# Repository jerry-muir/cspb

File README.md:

# Cluster System Power Board

## About

The Cluster System Power Board (CSPB) is a power distribution and control platform to simplify the construction of Single Board Computer Clusters. The power board is designed to allow for simple single cluster systems or complex multi board systems to be powered through one power supply and controlled from a single control module. Control of the power board is achieved via an i2c serial bus interface which can be chained across multiple power boards.
<br />

## The project
The project has three main components. The hardware design which can be found in the [Hardware](/Hardware) directory, the firmware code which can be found in the [Firmware](/Firmware) directory and some user interface software which can be found in the [Software](/Software) directory.

A detailed users manual can be found in the [Documents](\Documents)
 directory.
## Python package links:

[PIP cspb Package](https://pypi.org/project/cspb/)
<br />
[PIP cspb-tools Package](https://pypi.org/project/cspb-tools/)

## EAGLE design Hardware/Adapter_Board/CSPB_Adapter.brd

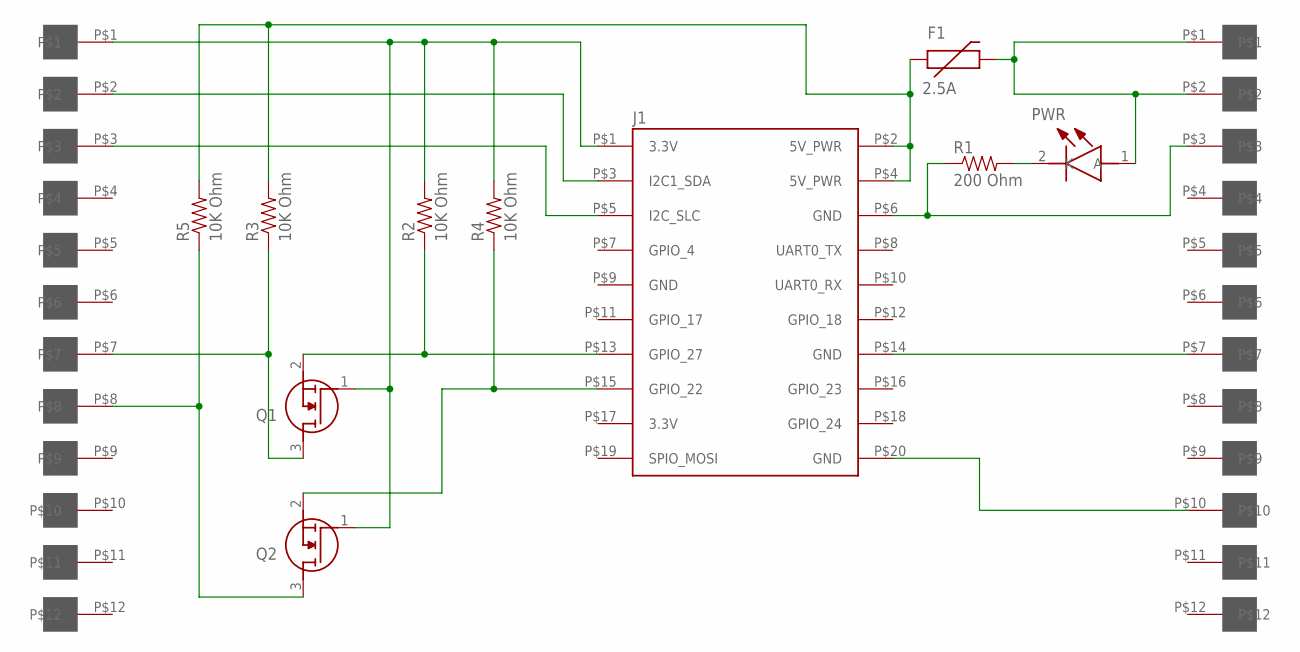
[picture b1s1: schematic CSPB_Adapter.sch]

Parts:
F1: 2.5A; F1812
J1: PPTC052LFBN-RC; 2X10_TH_HEADER_BOTTOM
J2, J3: 12_POS_BOARD_EDGE_PADS; CARD_EDGE_12_POS_0.1_IN
PWR: LTST-S220KGKT; LTSTS220KGKT
Q1, Q2: BSS138; SOT95P240X120-3N
R1: 200 Ohm; 0402-RES
R2, R3, R4, R5: 10K Ohm; 0402-RES

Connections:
3.3V: J1.P$1 (3.3V), J2.P$1, Q1.1 (G), Q2.1 (G), R2.2, R4.2
5V: F1.2, J3.P$1, J3.P$2, PWR.1 (A)
GND: J1.P$6 (GND), J1.P$9 (GND), J1.P$14 (GND), J1.P$20 (GND), J3.P$3, J3.P$7, J3.P$10, R1.1
MONITOR: J2.P$8, Q2.3 (D), R5.1
MONITOR_PI: J1.P$15 (GPIO_22), Q2.2 (S), R4.1
unnamed: F1.1, J1.P$2 (5V_PWR), J1.P$4 (5V_PWR), R3.2, R5.2
unnamed: PWR.2 (K), R1.2
SDA: J1.P$3 (I2C1_SDA), J2.P$2
SHUTDOWN: J2.P$7, Q1.3 (D), R3.1
SHUTDOWN_PI: J1.P$13 (GPIO_27), Q1.2 (S), R2.1
SLC: J1.P$5 (I2C_SLC), J2.P$3

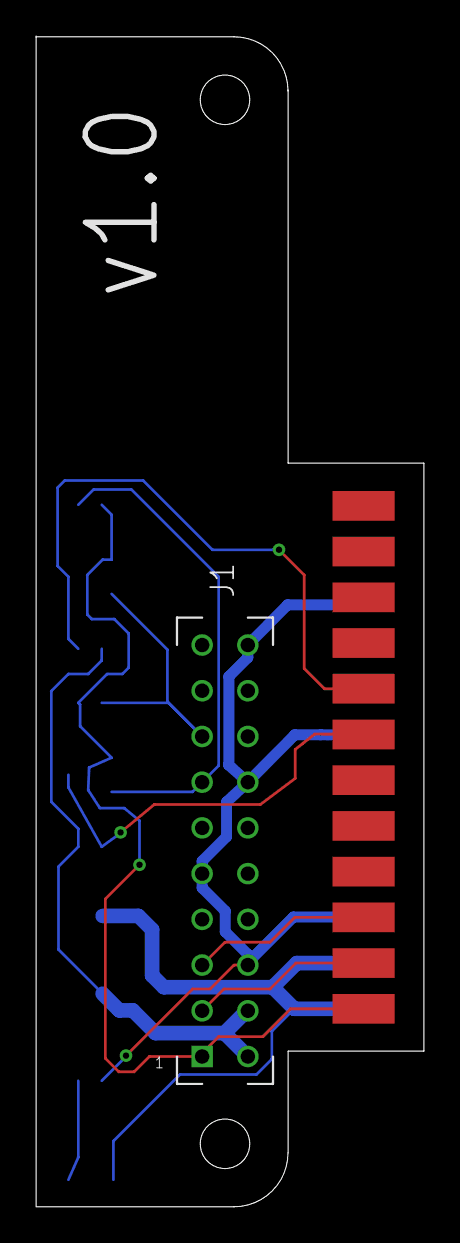
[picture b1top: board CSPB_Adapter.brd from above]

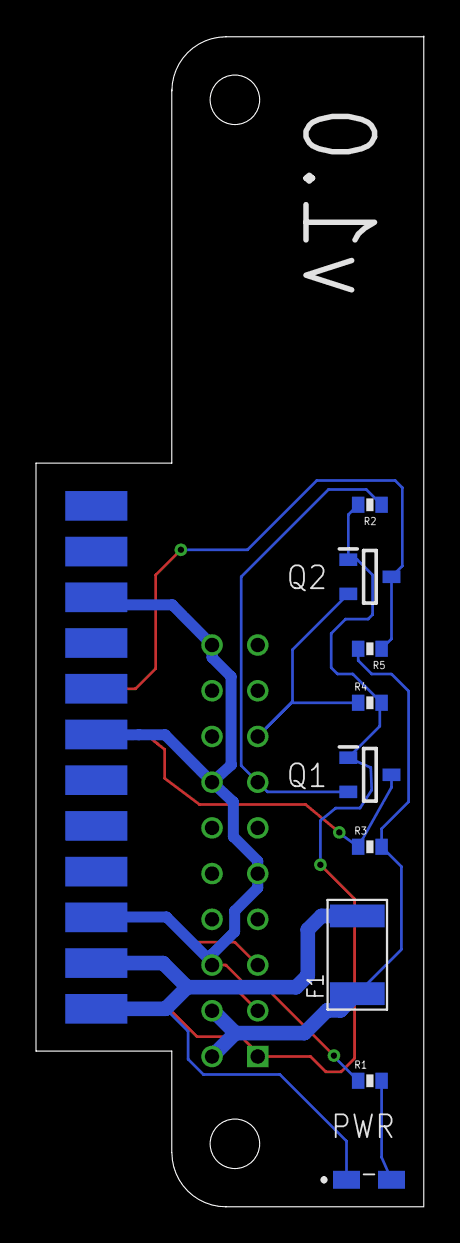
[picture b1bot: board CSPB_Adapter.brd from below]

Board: 2 copper layers, 21.6 x 65.0 mm, 12 parts (10 on the bottom side), 11 nets.

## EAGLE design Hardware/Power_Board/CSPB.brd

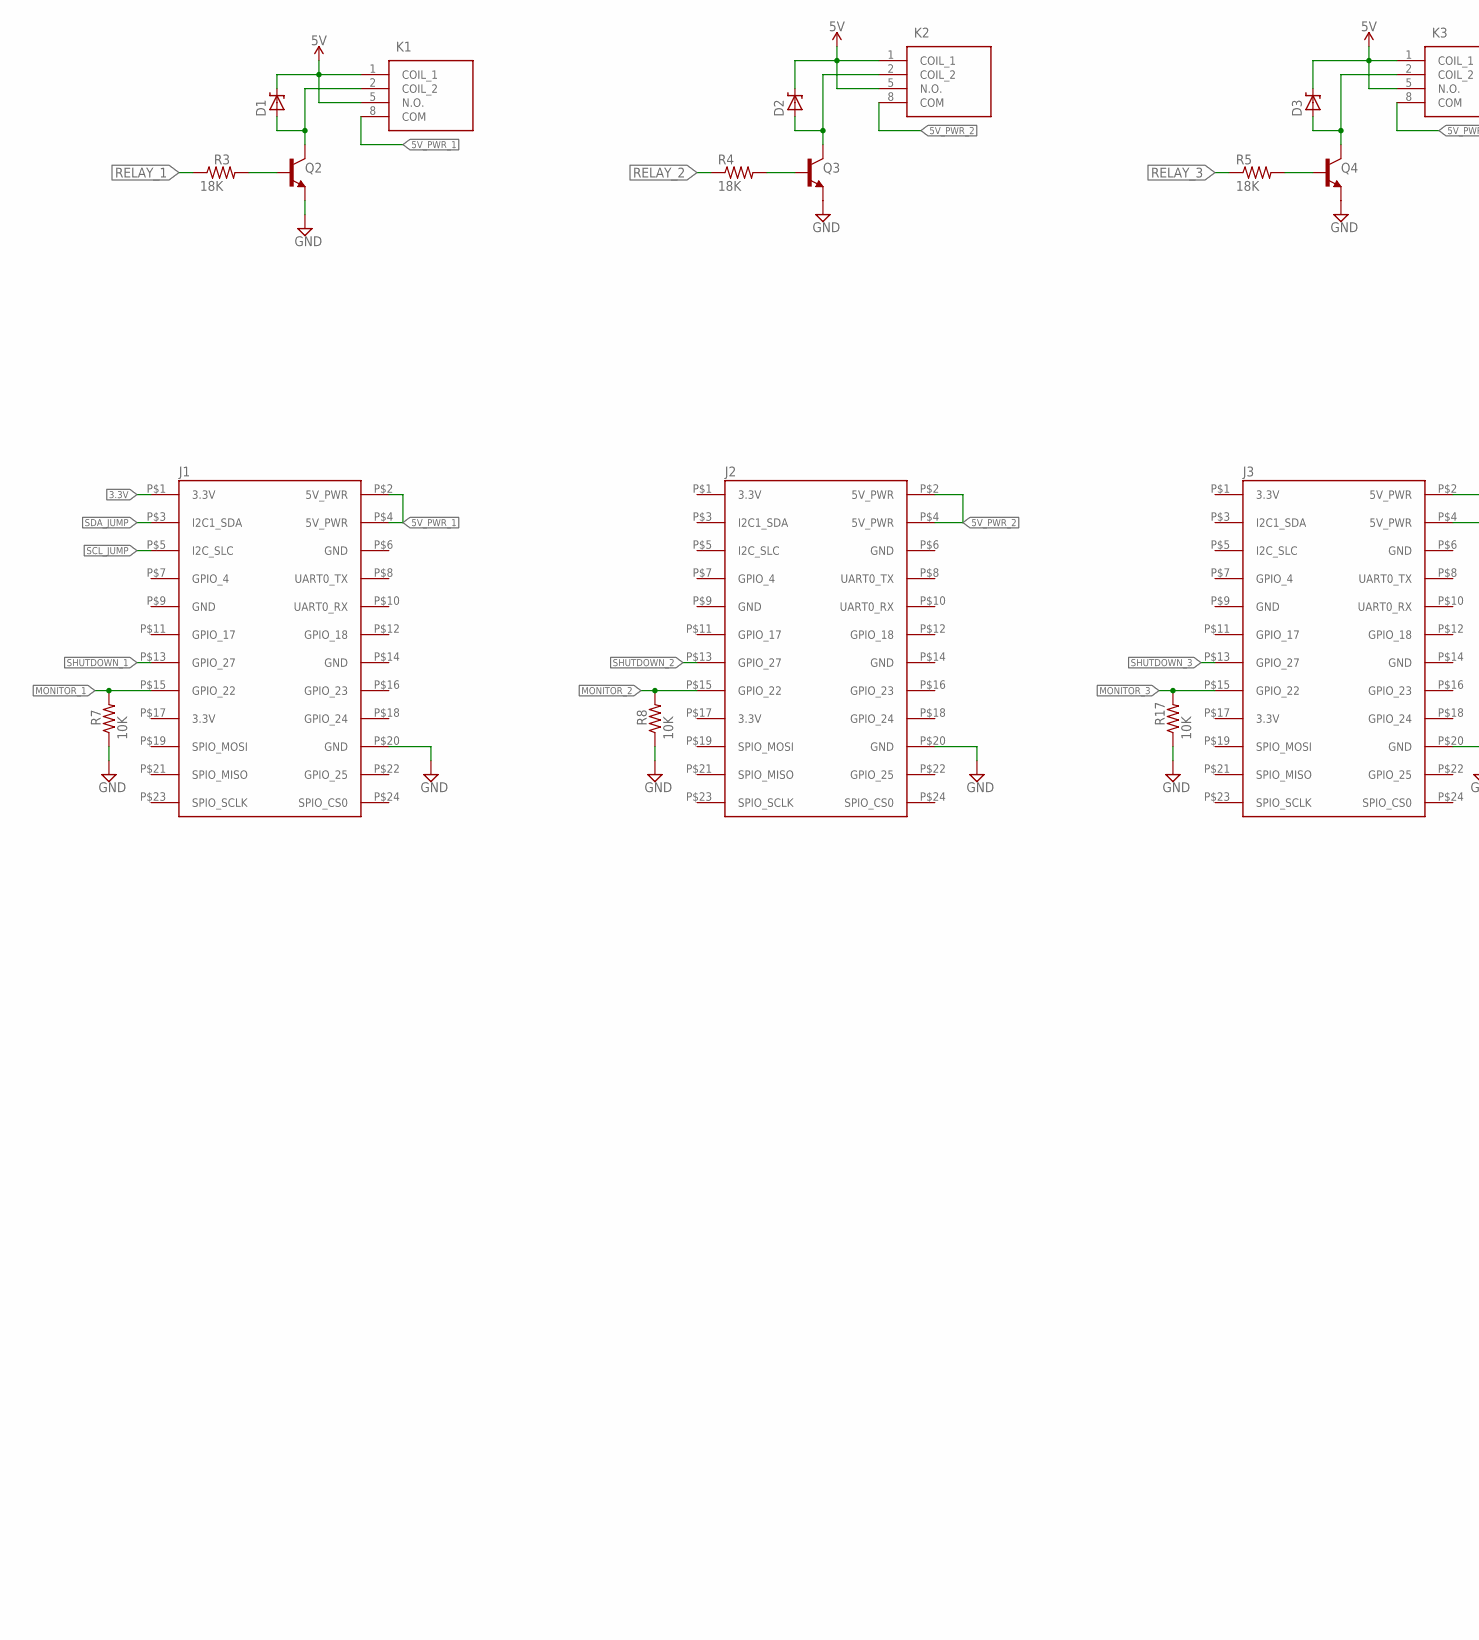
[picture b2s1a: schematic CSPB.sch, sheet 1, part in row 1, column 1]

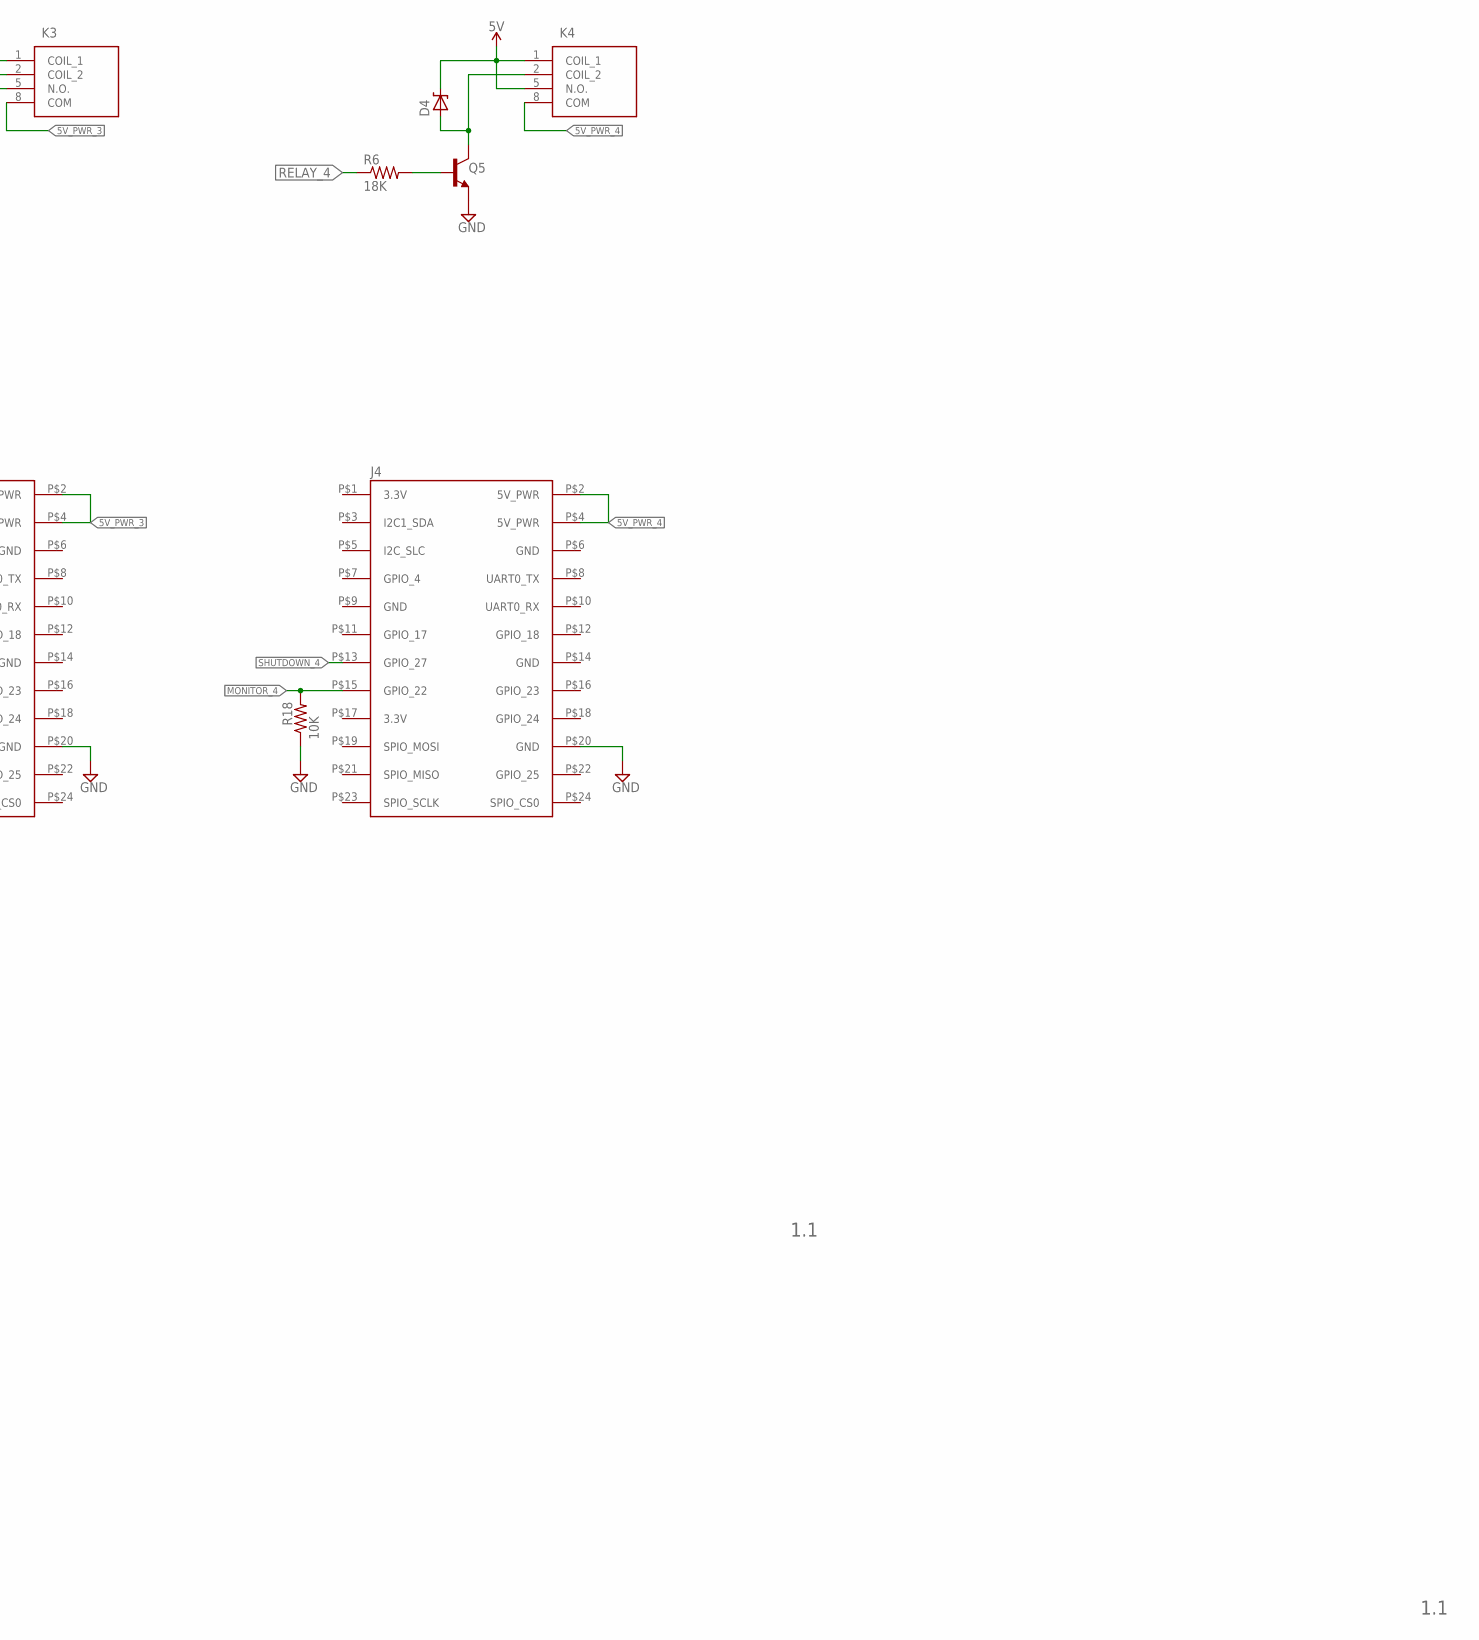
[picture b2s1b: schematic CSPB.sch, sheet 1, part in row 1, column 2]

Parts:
D1, D2, D3, D4: 1A/23V/620mV; SMADIODE
J1, J2, J3, J4: 5530843-1; 2X12_TH_EDGE_CONN
K1, K2, K3, K4: G6DN-1A_DC5; G6DN-1A-L
Q2, Q3, Q4, Q5: 600mA/40V; SOT23-3
R3, R4, R5, R6: 18K; 0603-RES
R7, R8, R17, R18: 10K; 0603-RES

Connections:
3.3V: J1.P$1 (3.3V); also elsewhere on the board
5V: D1.C, D2.C, D3.C, D4.C, K1.1 (COIL_1), K1.5 (N.O.), K2.1 (COIL_1), K2.5 (N.O.), K3.1 (COIL_1), K3.5 (N.O.), K4.1 (COIL_1), K4.5 (N.O.); also elsewhere on the board
5V_PWR_1: J1.P$2 (5V_PWR), J1.P$4 (5V_PWR), K1.8 (COM)
5V_PWR_2: J2.P$2 (5V_PWR), J2.P$4 (5V_PWR), K2.8 (COM)
5V_PWR_3: J3.P$2 (5V_PWR), J3.P$4 (5V_PWR), K3.8 (COM)
5V_PWR_4: J4.P$2 (5V_PWR), J4.P$4 (5V_PWR), K4.8 (COM)
GND: J1.P$6 (GND), J1.P$9 (GND), J1.P$14 (GND), J1.P$20 (GND), J2.P$6 (GND), J2.P$9 (GND), J2.P$14 (GND), J2.P$20 (GND), J3.P$6 (GND), J3.P$9 (GND), J3.P$14 (GND), J3.P$20 (GND), J4.P$6 (GND), J4.P$9 (GND), J4.P$14 (GND), J4.P$20 (GND), Q2.2 (E), Q3.2 (E), Q4.2 (E), Q5.2 (E), R7.1, R8.1, R17.1, R18.1; also elsewhere on the board
MONITOR_1: J1.P$15 (GPIO_22), R7.2; also elsewhere on the board
MONITOR_2: J2.P$15 (GPIO_22), R8.2; also elsewhere on the board
MONITOR_3: J3.P$15 (GPIO_22), R17.2; also elsewhere on the board
MONITOR_4: J4.P$15 (GPIO_22), R18.2; also elsewhere on the board
unnamed: Q2.1 (B), R3.2
unnamed: D1.A, K1.2 (COIL_2), Q2.3 (C)
unnamed: Q4.1 (B), R5.2
unnamed: Q5.1 (B), R6.2
unnamed: D2.A, K2.2 (COIL_2), Q3.3 (C)
unnamed: D3.A, K3.2 (COIL_2), Q4.3 (C)
unnamed: D4.A, K4.2 (COIL_2), Q5.3 (C)
unnamed: Q3.1 (B), R4.2
RELAY_1: R3.1; also elsewhere on the board
RELAY_2: R4.1; also elsewhere on the board
RELAY_3: R5.1; also elsewhere on the board
RELAY_4: R6.1; also elsewhere on the board
SCL_JUMP: J1.P$5 (I2C_SLC); also elsewhere on the board
SDA_JUMP: J1.P$3 (I2C1_SDA); also elsewhere on the board
SHUTDOWN_1: J1.P$13 (GPIO_27); also elsewhere on the board
SHUTDOWN_2: J2.P$13 (GPIO_27); also elsewhere on the board
SHUTDOWN_3: J3.P$13 (GPIO_27); also elsewhere on the board
SHUTDOWN_4: J4.P$13 (GPIO_27); also elsewhere on the board

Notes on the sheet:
1.1

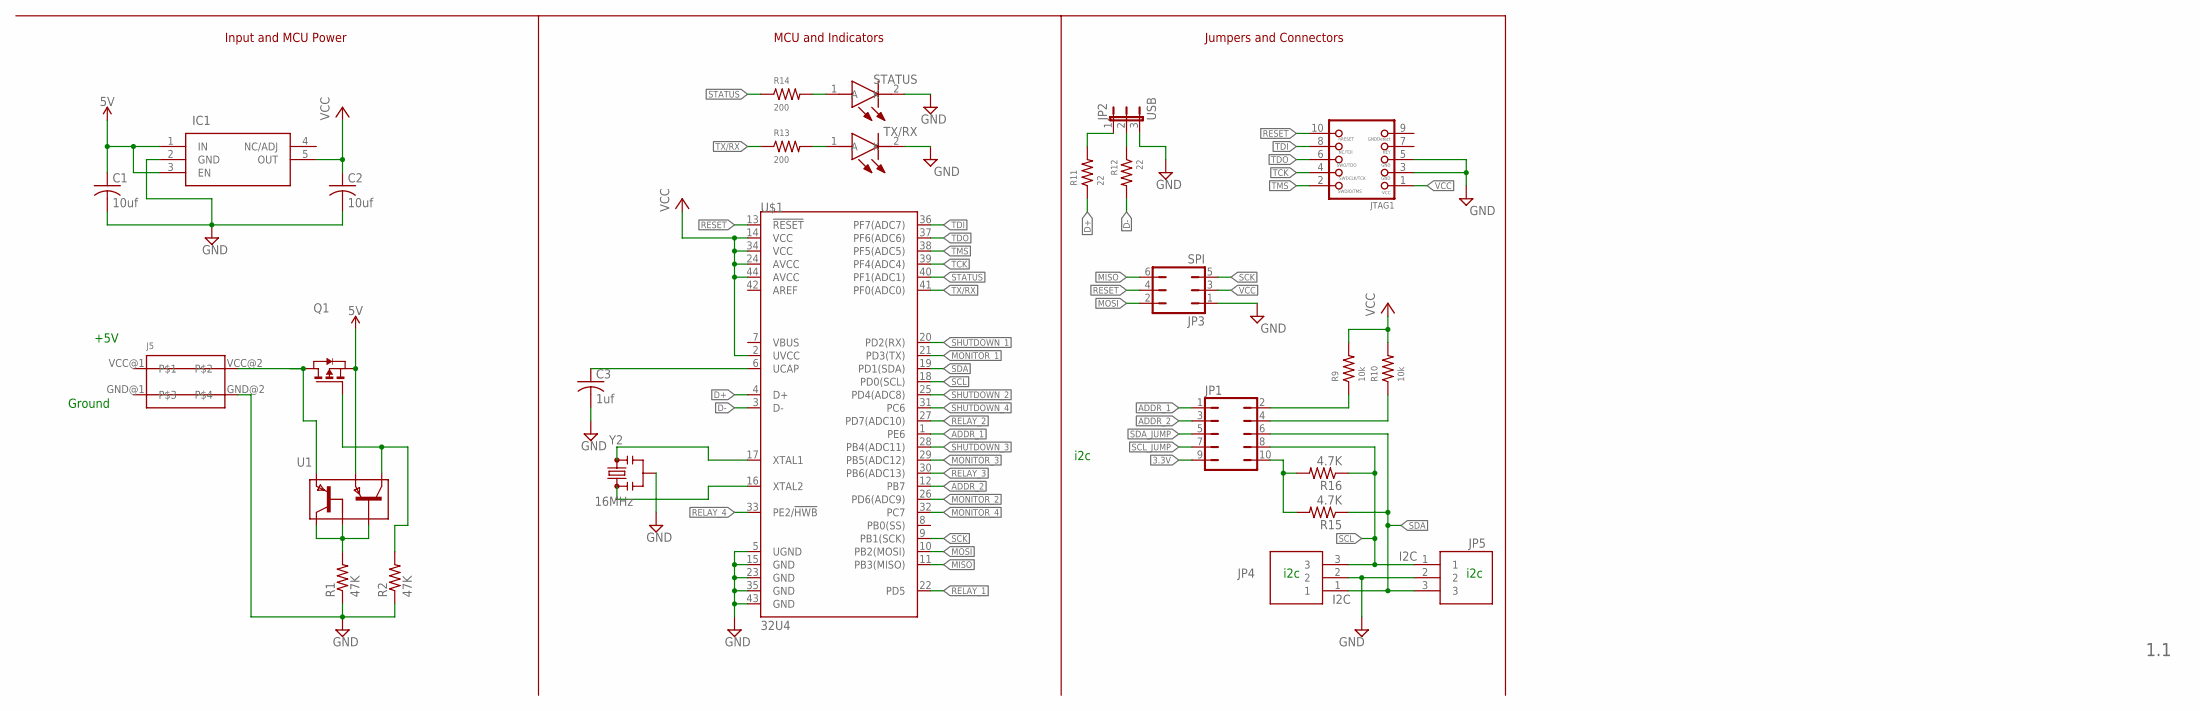
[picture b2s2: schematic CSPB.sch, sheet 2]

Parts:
C1, C2: 10uf; C1206
C3: 1uf; C1206
IC1: MIC5225-5.0YM5-TR; SOT95P280X130-5N
J5: 182442000; TB-2-POS-3_5MM-PITCH
JP1: JP5Q
JP2: USB; JUMPER3
JP3: SPI; JP3Q
JP4, JP5: I2C; SHDRRA3W50P0X200_1X3_790X760X4
JTAG1: JTAG-CORTEXM3MOLEX; CORTEXM3_SWD10_MOLEX
Q1: SQM40081EL; TO-263AB
R1, R2: 47K; 1206
R9, R10: 10k; 0402-RES
R11, R12: 22; 0402-RES
R13, R14: 200; 0805
R15, R16: 4.7K; 0603-RES
STATUS: LTST-S220KGKT; LTSTS220KGKT
TX/RX: LTST-S220KRKT; LTSTS220KGKT
U1: DMMT5401-7-F; SOT26-PNP
U$1: 32U4; QFN-44
Y2: 16MHz; RESONATOR-SMD-3.2X1.3

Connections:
3.3V: JP1.9; also elsewhere on the board
5V: C1.1, IC1.1 (IN), IC1.3 (EN), Q1.3 (S), U1.E2 (E1); also elsewhere on the board
ADDR_1: JP1.1, U$1.1 (PE6)
ADDR_2: JP1.3, U$1.12 (PB7)
D+: R11.1, U$1.4 (D+)
D-: R12.2, U$1.3 (D-)
GND: C1.2, C2.2, C3.2, IC1.2 (GND), J5.GND@2, JP2.3, JP3.1, JP4.2, JP5.2, JTAG1.3, JTAG1.5, R1.1, R2.1, STATUS.2 (K), TX/RX.2 (K), U$1.5 (UGND), U$1.15 (GND), U$1.23 (GND), U$1.35 (GND), U$1.43 (GND), Y2.2; also elsewhere on the board
MISO: JP3.6, U$1.11 (PB3(MISO))
MONITOR_1: U$1.21 (PD3(TX)); also elsewhere on the board
MONITOR_2: U$1.26 (PD6(ADC9)); also elsewhere on the board
MONITOR_3: U$1.29 (PB5(ADC12)); also elsewhere on the board
MONITOR_4: U$1.32 (PC7); also elsewhere on the board
MOSI: JP3.2, U$1.10 (PB2(MOSI))
unnamed: C3.1, U$1.6 (UCAP)
unnamed: R14.2, STATUS.1 (A)
unnamed: R13.2, TX/RX.1 (A)
unnamed: JP1.10, R15.2, R16.2
unnamed: R1.2, U1.B1 (B), U1.B2 (B1), U1.C1 (C)
unnamed: Q1.1 (G), R2.2, U1.C2 (C1)
unnamed: JP1.2, R9.1
unnamed: JP1.4, R10.1
unnamed: JP2.1, R11.2
unnamed: JP2.2, R12.1
P$1: J5.VCC@1
P$3: J5.GND@1
RELAY_1: U$1.22 (PD5); also elsewhere on the board
RELAY_2: U$1.27 (PD7(ADC10)); also elsewhere on the board
RELAY_3: U$1.30 (PB6(ADC13)); also elsewhere on the board
RELAY_4: U$1.33 (PE2/!HWB); also elsewhere on the board
RESET: JP3.4, JTAG1.10, U$1.13 (!RESET)
SCK: JP3.5, U$1.9 (PB1(SCK))
SCL: JP1.8, JP4.3, JP5.1, R16.1, U$1.18 (PD0(SCL))
SCL_JUMP: JP1.7; also elsewhere on the board
SDA: JP1.6, JP4.1, JP5.3, R15.1, U$1.19 (PD1(SDA))
SDA_JUMP: JP1.5; also elsewhere on the board
SHUTDOWN_1: U$1.20 (PD2(RX)); also elsewhere on the board
SHUTDOWN_2: U$1.25 (PD4(ADC8)); also elsewhere on the board
SHUTDOWN_3: U$1.28 (PB4(ADC11)); also elsewhere on the board
SHUTDOWN_4: U$1.31 (PC6); also elsewhere on the board
STATUS: R14.1, U$1.40 (PF1(ADC1))
TCK: JTAG1.4, U$1.39 (PF4(ADC4))
TDI: JTAG1.8, U$1.36 (PF7(ADC7))
TDO: JTAG1.6, U$1.37 (PF6(ADC6))
TMS: JTAG1.2, U$1.38 (PF5(ADC5))
TX/RX: R13.1, U$1.41 (PF0(ADC0))
VCC: C2.1, IC1.5 (OUT), JP3.3, JTAG1.1, R9.2, R10.2, U$1.2 (UVCC), U$1.14 (VCC), U$1.24 (AVCC), U$1.34 (VCC), U$1.44 (AVCC)
VCC_IN: J5.VCC@2, Q1.2 (D), U1.E1 (E)
XTAL1: U$1.17 (XTAL1), Y2.3
XTAL2: U$1.16 (XTAL2), Y2.1

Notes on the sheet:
i2c
+5V
Ground
Input and MCU Power
MCU and Indicators
Jumpers and Connectors
1.1

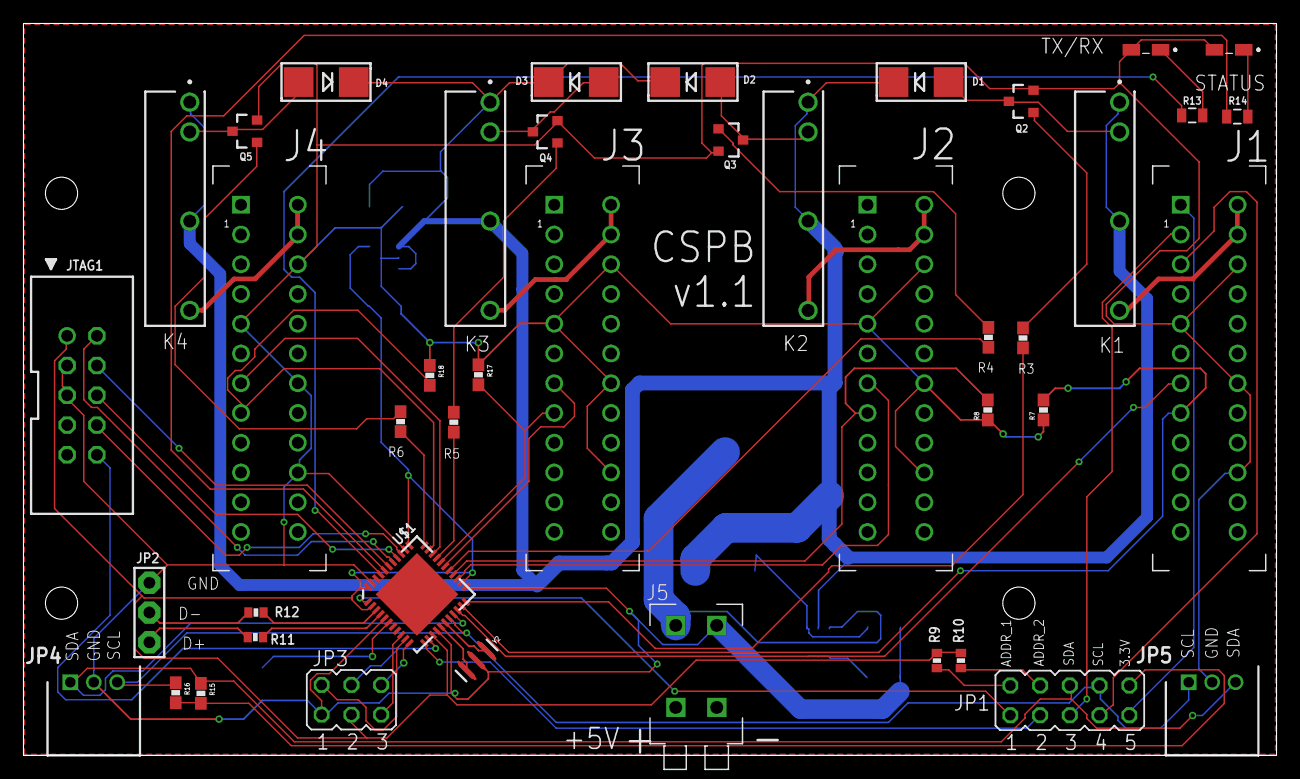
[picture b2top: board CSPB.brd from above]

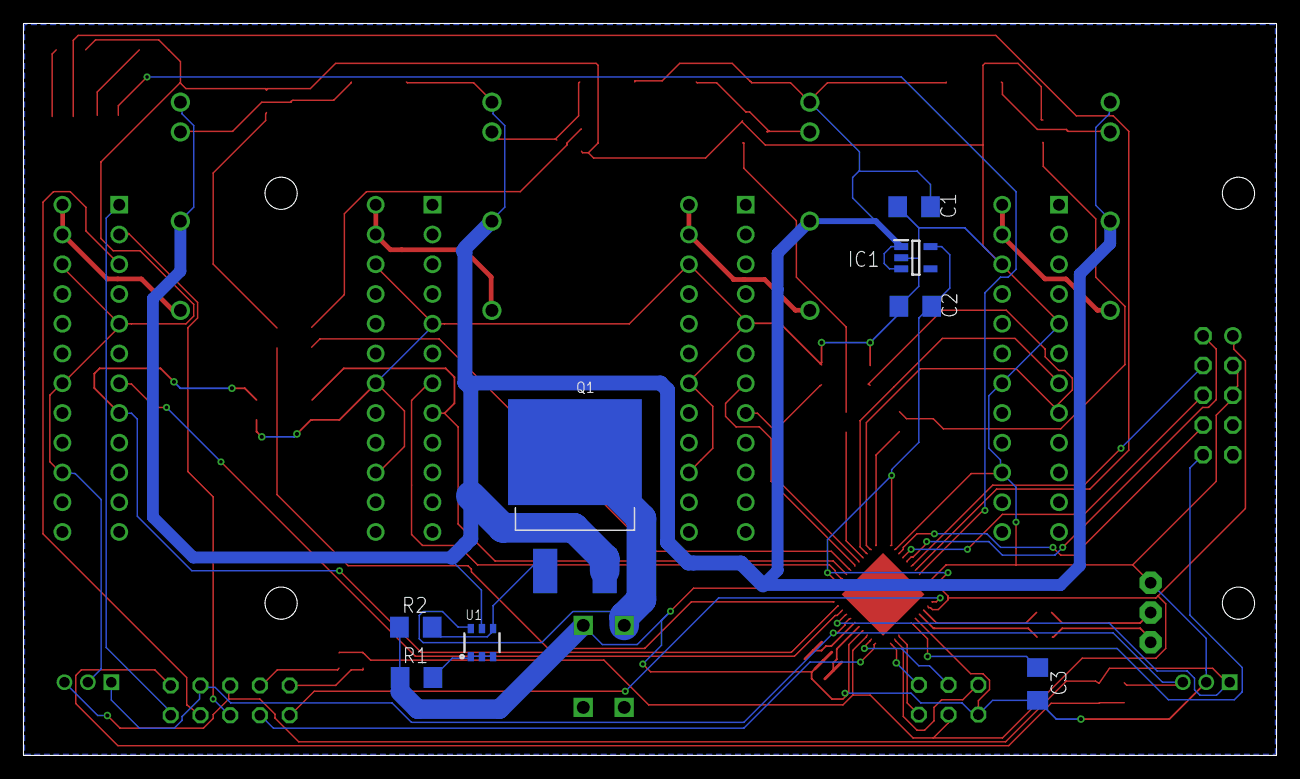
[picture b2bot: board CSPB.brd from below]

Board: 2 copper layers, 107.0 x 62.5 mm, 51 parts (8 on the bottom side), 59 nets.

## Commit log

2021-02-13 Create Documents
2021-02-13 Create Firmware
2021-02-13 Create Software
2021-02-13 Create Hardware
2021-02-17 Updated atmel project directory definitions to match git repoitory.
2021-02-18 Updated atmel project paths.
2021-02-18 - Added adapter board hardware design files.
2021-02-18 - Added Cluster System Power Board hardware design files.
2021-02-19 - Initial udate of the main README project file.
2021-02-19 - Update board picture to a more reasonable size.
2021-02-19 Create LICENSE
2021-02-19 Update LICENSE
    Use a product oriented license as there is more that must software here.
2021-02-19 - Center picture in readme file.
2021-02-21 - updateing user manual to v.1.1 to match current hardware files.

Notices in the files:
README.md:
License: MIT
parts and their libraries:
SparkFun: Licensing: CC v3.0 Share-Alike You are welcome to use this library for commercial purposes.
SparkFun-IC-Microcontroller: Licensing: Creative Commons ShareAlike 4.0 International - https://creativecommons.org/licenses/by-sa/4.0
